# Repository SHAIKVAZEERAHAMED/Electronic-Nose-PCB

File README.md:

# Electronic Nose System

A compact 14-channel MEMS-based Electronic Nose (E-Nose) platform designed for multi-gas sensing applications. The system integrates analog signal acquisition, dual-microcontroller processing, heater control, and battery-powered operation on a custom-designed PCB developed using KiCad.

---

## Overview

The Electronic Nose System is a modular hardware platform designed to interface with fourteen MEMS gas sensors for detecting a wide range of volatile organic compounds (VOCs) and hazardous gases. The design combines dedicated analog front-end circuits, a dual-microcontroller architecture, and an efficient power management subsystem into a compact printed circuit board.

The project focuses on hardware architecture, PCB implementation, and modular subsystem design to support future gas classification and pattern recognition algorithms.

---

## Key Features

- 14-channel MEMS gas sensor array
- ESP32-S3 WROOM 1 N16 main controller
- RP2040 dedicated PWM co-processor
- Configurable analog front-end
- Battery-powered operation
- Dual heater voltage rails (1.8 V and 2.5 V)
- BME680 environmental sensing
- KiCad 9.0.7 PCB design
- Modular hardware architecture

---

## System Architecture

```text
                    +----------------------+
                    |   MEMS Gas Sensors   |
                    +----------+-----------+
                               |
                               v
                    +----------------------+
                    |  Analog Front End    |
                    +----------+-----------+
                               ^
                               |
                              SPI
                               |
                               v
                    +----------------------+
                    |   ESP32-S3 (Master)  |
                    +----+--+---------+----+
                         |  ^         |
                         |  |         |
                      UART SPI       I²C/ADC
                         |  |         |
                         v  v         v
                  +--------------+  BME680
                  |    RP2040    |
                  +------+-------+
                         |
                         v
                +------------------+
                |  Heater Driver   |
                +--------+---------+
                         |
                         v
                +------------------+
                |  MEMS Heaters    |
                +------------------+

          Power Management supplies all modules
```

---
---

## PCB Layout

### Top View

### 3D View

---

## Hardware Specifications

| Component | Description |
|-----------|-------------|
| Gas Sensors | 14 MEMS Gas Sensors |
| Main Controller | ESP32-S3 WROOM 1 N16 |
| PWM Controller | RP2040 |
| Heater Driver | TBD62083AFNG |
| Environmental Sensor | BME680 |
| Analog Front End | TLV9152 |
| PCB Software | KiCad 9.0.7 |
| Power Source | Rechargeable Li-ion Battery |

---

## Repository Structure

```text
Electronic-Nose-PCB
│
├── Hardware
│   ├── Sensors
│   ├── Analog_Front_End
│   ├── ESP32-S3
│   ├── RP2040
│   ├── Power_Management
│   ├── PCB
│   └── KiCad_Project
│
├── Documentation
├── Datasheets
└── README.md
```
---

## Hardware

The hardware design is divided into modular subsystems:

- MEMS Gas Sensor Array
- Analog Front-End
- ESP32-S3 Processing Unit
- RP2040 PWM Controller
- Heater Driver
- Battery Management
- PCB Layout

---

## Software

| Tool | Purpose |
|------|---------|
| KiCad 9.0.7 | PCB Design |
| GitHub | Version Control |

---

## Project Status

🚧 Under Development

Current progress:

- ✅ System Architecture
- ✅ Schematic Design
- ⏳ PCB Layout
- ⏳ PCB Fabrication
- ⏳ Hardware Testing
- ⏳ Firmware Development

---

## License

This project is intended for academic and research purposes.

---

## Acknowledgment

This work was carried out at the International Institute of Information Technology Bangalore (IIIT Bangalore) under the guidance of Prof. Kurian Polachan. Technical guidance and discussions from Prof. David Aleklett Kadish and David Cuartielles (Malmö University and Arduino Co-founder) are gratefully acknowledged.

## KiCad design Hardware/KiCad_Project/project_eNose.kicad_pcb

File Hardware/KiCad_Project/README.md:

# KiCad Project

This directory contains the complete KiCad project files for the Electronic Nose hardware.

## Overview

The Electronic Nose PCB was designed using **KiCad 9.0.7**. This folder includes all project files required to open, edit, verify, and manufacture the PCB.

## Software Version

- KiCad 9.0.7

## Project Files

| File | Description |
|------|-------------|
| *.kicad_pro | KiCad project file |
| *.kicad_sch | Complete schematic |
| *.kicad_pcb | PCB layout |

## Design Features

- Multi-sheet schematic
- Fourteen-channel MEMS gas sensor array
- Dual microcontroller architecture
- Analog front-end circuitry
- Power management subsystem
- Single-layer PCB layout
- Design Rule Check (DRC) in progress
- Electrical Rule Check (ERC) verified

## How to Open

1. Install **KiCad 9.0.7** or later.
2. Open the `.kicad_pro` file.
3. Use the Schematic Editor to view the circuit design.
4. Use the PCB Editor to inspect or modify the layout.

## Folder Contents

This folder will contain:

- KiCad project
- Schematics
- PCB layout

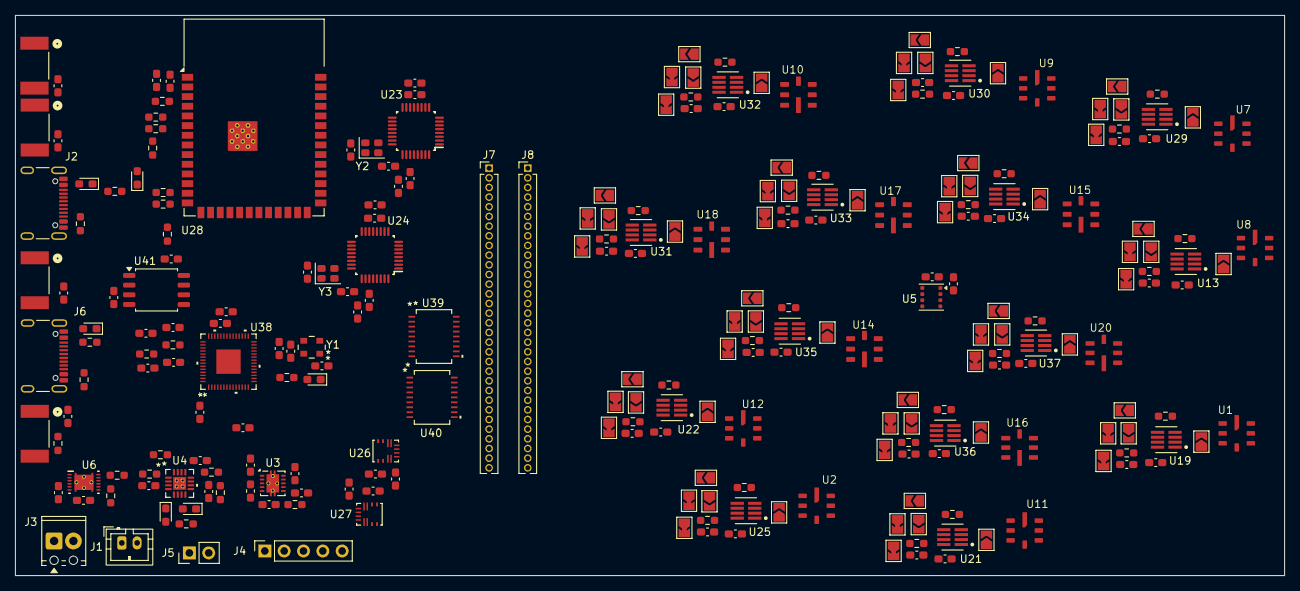
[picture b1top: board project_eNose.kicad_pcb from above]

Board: 2 copper layers, 166.7 x 73.6 mm, 262 parts (0 on the bottom side), 198 nets, no tracks yet.

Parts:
C1, C2, C4, C5, C9, C32, C41, C50: 0.1uF; C_0603_1608Metric_Pad1.08x0.95mm_HandSolder
C3, C60, C61, C62, C63, C64, C65, C66, C67, C68, C69, C70, C71, C72: 2.2nF; C_0603_1608Metric_Pad1.08x0.95mm_HandSolder
C6, C8, C10, C11, C12, C16, C17, C18, C19, C25, C26, C27, C31, C59: 10nF; C_0603_1608Metric_Pad1.08x0.95mm_HandSolder
C7, C13, C14, C20, C21, C22, C24: 10uF; C_0603_1608Metric_Pad1.08x0.95mm_HandSolder
C15, C23: 4.7uF; C_0603_1608Metric_Pad1.08x0.95mm_HandSolder
C28, C30, C38, C51, C52, C53, C54, C55, C56, C57, C58: 1uF; C_0603_1608Metric_Pad1.08x0.95mm_HandSolder
C29: 0.47uF; C_0603_1608Metric_Pad1.08x0.95mm_HandSolder
C33, C34, C35, C36, C37, C39, C40, C43, C44, C47, C73, C74: 100nF; C_0603_1608Metric_Pad1.08x0.95mm_HandSolder
C42: 22uF; C_0603_1608Metric_Pad1.08x0.95mm_HandSolder
C45, C46: 18pF; C_0603_1608Metric_Pad1.08x0.95mm_HandSolder
C48, C49: 220nF; C_0603_1608Metric_Pad1.08x0.95mm_HandSolder
D1, D2, D3, D4: LED; LED_0603_1608Metric_Pad1.05x0.95mm_HandSolder
D5, D6: D_Schottky; D_0603_1608Metric_Pad1.05x0.95mm_HandSolder
H1, H2, H3, H4: MountingHole; MountingHole_2mm
J1: Conn_01x02; JST_PH_B2B-PH-K_1x02_P2.00mm_Vertical
J2, J6: USB_C_Receptacle_USB2.0_16P; USB_C_Receptacle_GCT_USB4105-xx-A_16P_TopMnt_Horizontal
J3: Screw_Terminal_01x02; TerminalBlock_Phoenix_MPT-0,5-2-2.54_1x02_P2.54mm_Horizontal
J4: Conn_01x05; PinSocket_1x05_P2.54mm_Vertical
J5: Conn_01x02; PinHeader_1x02_P2.54mm_Vertical
J7, J8: Conn_01x32; PinHeader_1x32_P1.27mm_Vertical
JP1, JP2, JP45, JP46, JP47, JP48, JP49, JP50, JP51, JP52, JP53, JP54, JP55, JP56, JP57, JP58, JP59, JP60, JP61, JP62, JP63, JP64, JP65, JP66, JP67, JP68, JP69, JP70: SolderJumper_2_Bridged; SolderJumper-2_P1.3mm_Bridged_TrianglePad1.0x1.5mm_FIXED
JP3, JP4, JP5, JP6, JP7, JP8, JP9, JP10, JP11, JP12, JP13, JP14, JP15, JP16, JP17, JP18, JP19, JP20, JP21, JP22, JP23, JP24, JP25, JP26, JP27, JP28, JP29, JP30, JP31, JP32, JP33, JP34, JP35, JP36, JP37, JP38, JP39, JP40, JP41, JP42, JP43, JP44: SolderJumper_2_Open; SolderJumper-2_P1.3mm_Open_TrianglePad1.0x1.5mm
L1: 2.2uH; L_0603_1608Metric_Pad1.05x0.95mm_HandSolder
R1, R2, R4, R11, R15, R18, R19, R22, R23, R24, R25, R26, R27, R28, R29, R30, R31, R32, R33, R34, R35, R36, R37, R38, R39, R40, R41, R42, R43, R44, R45, R82: 10K; R_0603_1608Metric_Pad0.98x0.95mm_HandSolder
R3: 100E; R_0603_1608Metric_Pad0.98x0.95mm_HandSolder
R5, R6, R81: 1K; R_0603_1608Metric_Pad0.98x0.95mm_HandSolder
R7: 1.13K; R_0603_1608Metric_Pad0.98x0.95mm_HandSolder
R8: 1.18K; R_0603_1608Metric_Pad0.98x0.95mm_HandSolder
R9: 0.01; R_0603_1608Metric_Pad0.98x0.95mm_HandSolder
R10, R12, R13: 4.7K; R_0603_1608Metric_Pad0.98x0.95mm_HandSolder
R14: 820E; R_0603_1608Metric_Pad0.98x0.95mm_HandSolder
R16, R17: 22E; R_0603_1608Metric_Pad0.98x0.95mm_HandSolder
R20, R21, R52, R53: 5.1K; R_0603_1608Metric_Pad0.98x0.95mm_HandSolder
R79, R80: 27E; R_0603_1608Metric_Pad0.98x0.95mm_HandSolder
SW1, SW2, SW3, SW4: KSS221GLFS; SW_KSS221GLFS_CNK
U1, U2, U7, U8, U9, U11, U12: SMD_Series
U3: TPS63001; Texas_DRC0010J_ThermalVias
U4: BQ24075RGTR; RGT16_1P7X1P7
U5: BME680; Bosch_LGA-8_3x3mm_P0.8mm_ClockwisePinNumbering
U6: BQ27441DRZR-G1A; DRZ0012A
U10, U14, U15, U17, U18: GM_Series; GM102B
U13, U19, U21, U22, U25, U29, U30, U31, U32, U33, U34, U35, U36, U37: TLV9152; DDF0008A-IPC_A
U16, U20: GM_Series; GM202_502B
U23, U24: ADS131M08IPBSR; PBS0032A_L
U26: MPM3805GQB-25-Z; QFN2p5x3p0x0p9_MNP
U27: MPM3805GQB-18-P; QFN2p5x3p0x0p9_MNP
U28: ESP32-S3-WROOM-1-N16; ESP32-S3-WROOM-1
U38: SC091413; QFN56_7X7_RPI-L
U39, U40: TBD62083AFNG_EL; SSOP18-P-225-0p65_TOS-L
U41: W25Q32JVSS; SOIC-8_5.3x5.3mm_P1.27mm
Y1: ABM8G-12.000MHZ-18-D2Y-T; CRYSTAL_ABM8G_ABR-L
Y2, Y3: SG-210STF; Oscillator_SMD_SeikoEpson_SG210-4Pin_2.5x2.0mm

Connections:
1p8V: C22.1, C34.2, J7.31, J8.31, U1.1 (VH+), U2.1 (VH+), U7.1 (VH+), U8.1 (VH+), U9.1 (VH+), U10.1 (VH+), U11.1 (VH+), U12.1 (VH+), U18.1 (VH+), U27.5 (OUT), U27.6 (OUT), U27.12 (OUT_S), U41.8 (VCC)
2p5V: C20.1, J7.30, J8.30, U14.1 (VH+), U15.1 (VH+), U16.1 (VH+), U17.1 (VH+), U20.1 (VH+), U26.5 (OUT), U26.6 (OUT), U26.12 (OUT_S)
3p3V: C4.1, C5.1, C6.2, C8.2, C10.2, C11.2, C12.2, C13.1, C14.1, C16.2, C17.2, C18.2, C19.2, C25.2, C26.2, C27.2, C31.2, C33.2, C35.2, C36.2, C37.2, C38.2, C39.2, C40.2, C41.2, C42.2, C43.2, C44.2, C47.2, C51.2, C52.2, C53.2, C54.2, C55.2, C56.2, C57.2, C58.2, C59.2, C73.2, C74.1, J4.1, J7.29, J8.29, R10.1, R12.1, R13.1, R15.1, R82.2, U1.2 (VCC), U2.2 (VCC), U3.1 (VOUT), U3.10 (FB), U5.2 (CSB), U5.6 (VDDIO), U5.8 (VDD), U7.2 (VCC), U8.2 (VCC), U9.2 (VCC), U10.7 (VCC), U11.2 (VCC), U12.2 (VCC), U13.8 (V+), U14.7 (VCC), U15.7 (VCC), U16.7 (VCC), U17.7 (VCC), U18.7 (VCC), U19.8 (V+), U20.7 (VCC), U21.8 (V+), U22.8 (V+), U23.14 (REFIN), U23.15 (AVDD), U23.26 (IOVDD), U23.27 (AVDD), U24.14 (REFIN), U24.15 (AVDD), U24.26 (IOVDD), U24.27 (AVDD), U25.8 (V+), U28.2 (3V3), U29.8 (V+), U30.8 (V+), U31.8 (V+), U32.8 (V+), U33.8 (V+), U34.8 (V+), U35.8 (V+), U36.8 (V+), U37.8 (V+), U38.1 (IOVDD), U38.10 (IOVDD), U38.22 (IOVDD), U38.33 (IOVDD), U38.42 (IOVDD), U38.43 (ADC_AVDD), U38.44 (VREG_VIN), U38.48 (USB_VDD), U38.49 (IOVDD), Y2.4 (Vcc), Y3.4 (Vcc)
/Acetone/OUT1: JP16.1 (A), JP17.1 (A), U29.1 (1OUT), U29.2 (1IN-), U29.5 (2IN+)
/Alcohol/OUT1: JP34.1 (A), JP35.1 (A), U35.1 (1OUT), U35.2 (1IN-), U35.5 (2IN+)
/BME680 (Temp., Air, Humidity)/I2C.SCL: R13.2, U5.4 (SCK), U6.2 (SCL), U28.6 (IO6)
/BME680 (Temp., Air, Humidity)/I2C.SDA: R12.2, U5.3 (SDI), U6.1 (SDA), U28.5 (IO5)
/Breath Smell/OUT1: JP31.1 (A), JP32.1 (A), U34.1 (1OUT), U34.2 (1IN-), U34.5 (2IN+)
/CH4/OUT1: JP10.1 (A), JP11.1 (A), U22.1 (1OUT), U22.2 (1IN-), U22.5 (2IN+)
/Charger-Regulator/BatP: C15.1, C29.2, C30.1, J1.1, J3.1, J5.1, R9.1, U4.2 (BAT), U4.3 (BAT), U6.5 (VDD), U6.6 (BAT), U6.8 (SRP)
/Charger-Regulator/VIN: C28.1, D5.1 (K), D6.1 (K), U4.13 (IN)
/Charger-Regulator/VSYS: C7.1, C21.1, C23.1, C24.1, R3.1, R6.2, R9.2, U3.5 (VIN), U4.5 (EN2), U4.10 (OUT), U4.11 (OUT), U6.7 (SRN), U26.7 (VIN), U26.9 (EN), U27.7 (VIN), U27.9 (EN)
/H2/OUT1: JP28.1 (A), JP29.1 (A), U33.1 (1OUT), U33.2 (1IN-), U33.5 (2IN+)
/H2S & Benzene/OUT1: JP25.1 (A), JP26.1 (A), U32.1 (1OUT), U32.2 (1IN-), U32.5 (2IN+)
/H2S/OUT1: JP7.1 (A), JP8.1 (A), U25.1 (1OUT), U25.2 (1IN-), U25.5 (2IN+)
/HCHO/OUT1: JP3.1 (A), JP43.1 (A), U13.1 (1OUT), U13.2 (1IN-), U13.5 (2IN+)
/NH3/OUT1: JP4.1 (A), JP5.1 (A), U19.1 (1OUT), U19.2 (1IN-), U19.5 (2IN+)
/NO2/OUT1: JP22.1 (A), JP23.1 (A), U31.1 (1OUT), U31.2 (1IN-), U31.5 (2IN+)
/Perforated-Connectors/A0: C3.2, J7.1, J8.1, R23.2, U13.7 (2OUT), U23.29 (AIN0P)
/Perforated-Connectors/A1: C60.2, J7.2, J8.2, R11.2, U19.7 (2OUT), U23.32 (AIN1P)
/Perforated-Connectors/A2: C61.2, J7.3, J8.3, R19.2, U23.1 (AIN2P), U25.7 (2OUT)
/Perforated-Connectors/A3: C62.2, J7.4, J8.4, R25.2, U22.7 (2OUT), U23.4 (AIN3P)
/Perforated-Connectors/A4: C63.2, J7.5, J8.5, R27.2, U21.7 (2OUT), U23.5 (AIN4P)
/Perforated-Connectors/A5: C64.2, J7.6, J8.6, R29.2, U23.8 (AIN5P), U29.7 (2OUT)
/Perforated-Connectors/A6: C65.2, J7.7, J8.7, R31.2, U23.9 (AIN6P), U30.7 (2OUT)
/Perforated-Connectors/A7: C66.2, J7.8, J8.8, R33.2, U24.29 (AIN0P), U31.7 (2OUT)
/Perforated-Connectors/A8: C67.2, J7.9, J8.9, R35.2, U24.32 (AIN1P), U32.7 (2OUT)
/Perforated-Connectors/A9: C68.2, J7.10, J8.10, R37.2, U24.1 (AIN2P), U33.7 (2OUT)
/Perforated-Connectors/A10: C69.2, J7.11, J8.11, R39.2, U24.4 (AIN3P), U34.7 (2OUT)
/Perforated-Connectors/A11: C70.2, J7.12, J8.12, R41.2, U24.5 (AIN4P), U35.7 (2OUT)
/Perforated-Connectors/A12: C71.2, J7.13, J8.13, R43.2, U24.8 (AIN5P), U36.7 (2OUT)
/Perforated-Connectors/A13: C72.2, J7.14, J8.14, R45.2, U24.9 (AIN6P), U37.7 (2OUT)
/Perforated-Connectors/HOT0: J7.15, J8.15, U8.7 (HOT), U39.18 (O1)
/Perforated-Connectors/HOT1: J7.16, J8.16, U1.7 (HOT), U39.17 (O2)
/Perforated-Connectors/HOT2: J7.17, J8.17, U2.7 (HOT), U39.16 (O3)
/Perforated-Connectors/HOT3: J7.18, J8.18, U12.7 (HOT), U39.15 (O4)
/Perforated-Connectors/HOT4: J7.19, J8.19, U11.7 (HOT), U39.14 (O5)
/Perforated-Connectors/HOT5: J7.20, J8.20, U7.7 (HOT), U39.13 (O6)
/Perforated-Connectors/HOT6: J7.21, J8.21, U9.7 (HOT), U39.12 (O7)
/Perforated-Connectors/HOT7: J7.22, J8.22, U18.3 (HOT), U40.18 (O1)
/Perforated-Connectors/HOT8: J7.23, J8.23, U10.3 (HOT), U40.17 (O2)
/Perforated-Connectors/HOT9: J7.24, J8.24, U17.3 (HOT), U40.16 (O3)
/Perforated-Connectors/HOT10: J7.25, J8.25, U15.3 (HOT), U40.15 (O4)
/Perforated-Connectors/HOT11: J7.26, J8.26, U14.3 (HOT), U40.14 (O5)
/Perforated-Connectors/HOT12: J7.27, J8.27, U16.3 (HOT), U40.13 (O6)
/Perforated-Connectors/HOT13: J7.28, J8.28, U20.3 (HOT), U40.12 (O7)
/Propane/OUT1: JP13.1 (A), JP14.1 (A), U21.1 (1OUT), U21.2 (1IN-), U21.5 (2IN+)
/RP2040/CLK: U38.52 (SQPI_SCLK), U41.6 (CLK)
/RP2040/CS: U38.56 (SQPI_SS_N), U41.1 (~CS)
/RP2040/DVDD: U38.23 (DVDD), U38.45 (VREG_VOUT), U38.50 (DVDD)
/RP2040/IO0: U38.53 (SQPI_SD0), U41.5 (DI/IO_{0})
/RP2040/IO1: U38.55 (SQPI_SD1), U41.2 (DO/IO_{1})
/RP2040/IO2: U38.54 (SQPI_SD2), U41.3 (~WP/IO_{2})
/RP2040/IO3: U38.51 (SQPI_SD3), U41.7 (~HOLD/~RESET/IO_{3})
/RP2040/PWM0: U38.2 (GPIO0), U39.1 (I1)
/RP2040/PWM1: U38.3 (GPIO1), U39.2 (I2)
/RP2040/PWM2: U38.4 (GPIO2), U39.3 (I3)
/RP2040/PWM3: U38.5 (GPIO3), U39.4 (I4)
/RP2040/PWM4: U38.6 (GPIO4), U39.5 (I5)
/RP2040/PWM5: U38.7 (GPIO5), U39.6 (I6)
/RP2040/PWM6: U38.8 (GPIO6), U39.7 (I7)
/RP2040/PWM7: U38.9 (GPIO7), U40.1 (I1)
/RP2040/PWM8: U38.11 (GPIO8), U40.2 (I2)
/RP2040/PWM9: U38.12 (GPIO9), U40.3 (I3)
/RP2040/PWM10: U38.13 (GPIO10), U40.4 (I4)
/RP2040/PWM11: U38.14 (GPIO11), U40.5 (I5)
/RP2040/PWM12: U38.15 (GPIO12), U40.6 (I6)
/RP2040/PWM13: U38.16 (GPIO13), U40.7 (I7)
/RP2040/RUN_RESET: C32.2, J4.5, R82.1, SW3.2, U38.26 (RUN)
/RP2040/SPI0: U28.39 (IO1), U38.32 (GPIO21)
/RP2040/SPI1: U28.38 (IO2), U38.31 (GPIO20)
/RP2040/SPI2: U28.10 (IO17), U38.30 (GPIO19)
/RP2040/SPI3: U28.11 (IO18), U38.29 (GPIO18)
/RP2040/SWD_IO: J4.3, U38.25 (SWDIO)
/RP2040/SW_CLK: J4.4, U38.24 (SWCLK)
/RP2040/UART.Rx: U28.37 (TXD0), U38.28 (GPIO17)
/RP2040/UART.Tx: U28.36 (RXD0), U38.27 (GPIO16)
/RP2040/USB1.Dm: J6.A7 (D-), J6.B7 (D-), R80.1
/RP2040/USB1.Dp: J6.A6 (D+), J6.B6 (D+), R79.2
/RP2040/XIN: C45.2, U38.20 (XIN), Y1.1
/RP2040/XOUT: C46.2, U38.21 (XOUT), Y1.3
/Smoke/OUT1: JP37.1 (A), JP38.1 (A), U36.1 (1OUT), U36.2 (1IN-), U36.5 (2IN+)
/TVOC/OUT1: JP19.1 (A), JP20.1 (A), U30.1 (1OUT), U30.2 (1IN-), U30.5 (2IN+)
/VOC/OUT1: JP40.1 (A), JP41.1 (A), U37.1 (1OUT), U37.2 (1IN-), U37.5 (2IN+)
/bat-conn-Monitor/GPOUT: R10.2, U6.12 (GPOUT), U28.15 (IO3)
/esp/Analog -> SPI/A_SPI0: U23.21 (DIN), U24.21 (DIN), U28.19 (IO11)
/esp/Analog -> SPI/A_SPI1: U23.20 (DOUT), U24.20 (DOUT), U28.21 (IO13)
/esp/Analog -> SPI/A_SPI2: U23.19 (SCLK), U24.19 (SCLK), U28.20 (IO12)
/esp/Analog -> SPI/A_SPI3: U23.18 (DRDY_N), U28.17 (IO9)
/esp/Analog -> SPI/A_SPI4: U23.17 (CS_N), U28.18 (IO10)
/esp/Analog -> SPI/A_SPI5: U23.16 (SYNC_RESET_N), U28.12 (IO8)
/esp/Analog -> SPI/A_SPI6: U24.18 (DRDY_N), U28.22 (IO14)
/esp/Analog -> SPI/A_SPI7: U24.17 (CS_N), U28.8 (IO15)
/esp/Analog -> SPI/A_SPI8: U24.16 (SYNC_RESET_N), U28.9 (IO16)
/esp/Analog -> SPI/CLKIN1: U23.23 (XTAL1_CLKIN), Y2.3 (OUT)
/esp/Analog -> SPI/CLKIN2: U24.23 (XTAL1_CLKIN), Y3.3 (OUT)
/esp/EN: C1.2, C2.2, R15.2, SW1.2, SW2.2, U28.3 (EN), U28.27 (IO0)
/esp/USB0.Dm: J2.A7 (D-), J2.B7 (D-), R17.1
/esp/USB0.Dp: J2.A6 (D+), J2.B6 (D+), R16.2
/esp/user_sw: C50.2, SW4.2, U28.4 (IO4)
GND: C1.1, C2.1, C4.2, C5.2, C6.1, C7.2, C8.1, C9.2, C10.1, C11.1, C12.1, C13.2, C14.2, C15.2, C16.1, C17.1, C18.1, C19.1, C20.2, C21.2, C22.2, C23.2, C24.2, C25.1, C26.1, C27.1, C28.2, C29.1, C30.2, C31.1, C32.1, C33.1, C34.1, C35.1, C36.1, C37.1, C38.1, C39.1, C40.1, C41.1, C42.1, C43.1, C44.1, C45.1, C46.1, C47.1, C48.1, C49.1, C50.1, C51.1, C52.1, C53.1, C54.1, C55.1, C56.1, C57.1, C58.1, C59.1, C73.1, C74.2, D1.1 (K), D4.1 (K), J1.2, J2.A1 (GND), J2.A12 (GND), J2.B1 (GND), J2.B12 (GND), J2.S1 (SHIELD), J3.2, J4.2, J5.2, J6.A1 (GND), J6.A12 (GND), J6.B1 (GND), J6.B12 (GND), J6.S1 (SHIELD), J7.32, J8.32, R1.1, R2.1, R4.1, R7.1, R8.1, R18.1, R20.2, R21.1, R22.1, R24.1, R26.1, R28.1, R30.1, R32.1, R34.1, R36.1, R38.1, R40.1, R42.1, R44.1, R52.2, R53.1, SW1.1, SW2.1, SW3.1, SW4.1, U3.3 (PGND), U3.9 (GND), U3.11 (PGND), U4.4 (*CE), U4.6 (EN1), U4.8 (VSS), U4.14 (TMR), U4.15 (SYSOFF), U4.17 (EPAD), U5.1 (GND), U5.5 (SDO), U5.7 (GND), U6.3 (VSS), U6.13 (PAD), U13.4 (V-), U19.4 (V-), U21.4 (V-), U22.4 (V-), U23.2 (AIN2N), U23.3 (AIN3N), U23.6 (AIN4N), U23.7 (AIN5N), U23.10 (AIN6N), U23.11 (AIN7N), U23.12 (AIN7P), U23.13 (AGND_REFGND), U23.25 (DGND), U23.28 (AGND), U23.30 (AIN0N), U23.31 (AIN1N), U24.2 (AIN2N), U24.3 (AIN3N), U24.6 (AIN4N), U24.7 (AIN5N), U24.10 (AIN6N), U24.11 (AIN7N), U24.12 (AIN7P), U24.13 (AGND_REFGND), U24.25 (DGND), U24.28 (AGND), U24.30 (AIN0N), U24.31 (AIN1N), U25.4 (V-), U26.1 (PGND), U26.2 (PGND), U26.11 (AGND), U27.1 (PGND), U27.2 (PGND), U27.11 (AGND), U28.1 (GND), U28.40 (GND), U28.41 (GND), U29.4 (V-), U30.4 (V-), U31.4 (V-), U32.4 (V-), U33.4 (V-), U34.4 (V-), U35.4 (V-), U36.4 (V-), U37.4 (V-), U38.19 (TESTEN), U38.35 (GPIO23), U38.57 (GND), U39.9 (GND), U40.9 (GND), U41.4 (GND), Y1.2, Y1.4, Y2.1 (~ST), Y2.2 (GND), Y3.1 (~ST), Y3.2 (GND)
unnamed: D1.2 (A), R14.2
unnamed: D2.2 (A), R5.2
unnamed: D2.1 (K), U4.7 (*PGOOD)
unnamed: D3.2 (A), R5.1, R6.1
unnamed: D3.1 (K), U4.9 (*CHG)
unnamed: D4.2 (A), R81.2
unnamed: D5.2 (A), J6.A4 (VBUS), J6.A9 (VBUS), J6.B4 (VBUS), J6.B9 (VBUS)
unnamed: D6.2 (A), J2.A4 (VBUS), J2.A9 (VBUS), J2.B4 (VBUS), J2.B9 (VBUS)
unnamed: J2.A5 (CC1), R20.1
unnamed: J2.B5 (CC2), R21.2
unnamed: J6.A5 (CC1), R52.1
unnamed: J6.B5 (CC2), R53.2
unnamed: JP1.1 (A), JP2.1 (A), JP43.2 (B), JP44.2 (B), U13.6 (2IN-)
unnamed: JP1.2 (B), R23.1
unnamed: C3.1, JP2.2 (B)
unnamed: JP3.2 (B), U8.8 (VOUT), U13.3 (1IN+)
unnamed: JP4.2 (B), U1.8 (VOUT), U19.3 (1IN+)
unnamed: JP6.1 (A), R2.2
unnamed: JP7.2 (B), U2.8 (VOUT), U25.3 (1IN+)
unnamed: JP9.1 (A), R18.2
unnamed: JP10.2 (B), U12.8 (VOUT), U22.3 (1IN+)
unnamed: JP11.2 (B), JP12.2 (B), JP49.1 (A), JP50.1 (A), U22.6 (2IN-)
unnamed: JP12.1 (A), R24.2
unnamed: JP13.2 (B), U11.8 (VOUT), U21.3 (1IN+)
unnamed: JP14.2 (B), JP15.2 (B), JP51.1 (A), JP52.1 (A), U21.6 (2IN-)
unnamed: JP15.1 (A), R26.2
unnamed: JP16.2 (B), U7.8 (VOUT), U29.3 (1IN+)
unnamed: JP17.2 (B), JP18.2 (B), JP53.1 (A), JP54.1 (A), U29.6 (2IN-)
unnamed: JP18.1 (A), R28.2
unnamed: JP19.2 (B), U9.8 (VOUT), U30.3 (1IN+)
unnamed: JP20.2 (B), JP21.2 (B), JP55.1 (A), JP56.1 (A), U30.6 (2IN-)
unnamed: JP21.1 (A), R30.2
unnamed: JP22.2 (B), U18.5 (VOUT), U31.3 (1IN+)
unnamed: JP23.2 (B), JP24.2 (B), JP57.1 (A), JP58.1 (A), U31.6 (2IN-)
unnamed: JP24.1 (A), R32.2
unnamed: JP25.2 (B), U10.5 (VOUT), U32.3 (1IN+)
unnamed: JP26.2 (B), JP27.2 (B), JP59.1 (A), JP60.1 (A), U32.6 (2IN-)
unnamed: JP27.1 (A), R34.2
unnamed: JP28.2 (B), U17.5 (VOUT), U33.3 (1IN+)
unnamed: JP29.2 (B), JP30.2 (B), JP61.1 (A), JP62.1 (A), U33.6 (2IN-)
unnamed: JP30.1 (A), R36.2
unnamed: JP31.2 (B), U15.5 (VOUT), U34.3 (1IN+)
unnamed: JP32.2 (B), JP33.2 (B), JP63.1 (A), JP64.1 (A), U34.6 (2IN-)
unnamed: JP33.1 (A), R38.2
unnamed: JP34.2 (B), U14.5 (VOUT), U35.3 (1IN+)
unnamed: JP35.2 (B), JP36.2 (B), JP65.1 (A), JP66.1 (A), U35.6 (2IN-)
unnamed: JP36.1 (A), R40.2
unnamed: JP37.2 (B), U16.5 (VOUT), U36.3 (1IN+)
unnamed: JP38.2 (B), JP39.2 (B), JP67.1 (A), JP68.1 (A), U36.6 (2IN-)
unnamed: JP39.1 (A), R42.2
unnamed: JP40.2 (B), U20.5 (VOUT), U37.3 (1IN+)
unnamed: JP41.2 (B), JP42.2 (B), JP69.1 (A), JP70.1 (A), U37.6 (2IN-)
unnamed: JP42.1 (A), R44.2
unnamed: JP44.1 (A), R22.2
unnamed: JP5.2 (B), JP6.2 (B), JP45.1 (A), JP46.1 (A), U19.6 (2IN-)
unnamed: JP45.2 (B), R11.1
unnamed: C60.1, JP46.2 (B)
unnamed: JP8.2 (B), JP9.2 (B), JP47.1 (A), JP48.1 (A), U25.6 (2IN-)
unnamed: JP47.2 (B), R19.1
unnamed: C61.1, JP48.2 (B)
unnamed: JP49.2 (B), R25.1
unnamed: C62.1, JP50.2 (B)
unnamed: JP51.2 (B), R27.1
unnamed: C63.1, JP52.2 (B)
unnamed: JP53.2 (B), R29.1
unnamed: C64.1, JP54.2 (B)
unnamed: JP55.2 (B), R31.1
unnamed: C65.1, JP56.2 (B)
unnamed: JP57.2 (B), R33.1
unnamed: C66.1, JP58.2 (B)
unnamed: JP59.2 (B), R35.1
unnamed: C67.1, JP60.2 (B)
unnamed: JP61.2 (B), R37.1
unnamed: C68.1, JP62.2 (B)
unnamed: JP63.2 (B), R39.1
unnamed: C69.1, JP64.2 (B)
unnamed: JP65.2 (B), R41.1
unnamed: C70.1, JP66.2 (B)
unnamed: JP67.2 (B), R43.1
unnamed: C71.1, JP68.2 (B)
unnamed: JP69.2 (B), R45.1
unnamed: C72.1, JP70.2 (B)
unnamed: C9.1, R3.2, U3.6 (EN), U3.7 (PS/SYNC), U3.8 (VINA)
unnamed: L1.2, U3.4 (L1)
unnamed: L1.1, U3.2 (L2)
unnamed: R8.2, U4.12 (ILIM)
unnamed: R7.2, U4.16 (ISET)
unnamed: R4.2, U4.1 (TS)
unnamed: R1.2, U6.10 (BIN)
unnamed: C48.2, U23.24 (LDOCAP)
unnamed: C49.2, U24.24 (LDOCAP)
unnamed: R14.1, U28.7 (IO7)
unnamed: R17.2, U28.14 (USB_D+)
unnamed: R16.1, U28.13 (USB_D-)
unnamed: R81.1, U38.17 (GPIO14)
unnamed: R80.2, U38.46 (USB_DM)
unnamed: R79.1, U38.47 (USB_DP)

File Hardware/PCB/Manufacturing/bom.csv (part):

"Reference","Value","Footprint","myMANUFACTURER","myMPN"
"C1","0.1uF","Capacitor_SMD:C_0603_1608Metric_Pad1.08x0.95mm_HandSolder","YAGEO","CC0603MRY5V9BB104"
"C2","0.1uF","Capacitor_SMD:C_0603_1608Metric_Pad1.08x0.95mm_HandSolder","YAGEO","CC0603MRY5V9BB104"
"C3","2.2nF","Capacitor_SMD:C_0603_1608Metric_Pad1.08x0.95mm_HandSolder","KEMET","C0603X222F4HACTU"
"C4","0.1uF","Capacitor_SMD:C_0603_1608Metric_Pad1.08x0.95mm_HandSolder","YAGEO","CC0603MRY5V9BB104"
"C5","0.1uF","Capacitor_SMD:C_0603_1608Metric_Pad1.08x0.95mm_HandSolder","YAGEO","CC0603MRY5V9BB104"
"C6","10nF","Capacitor_SMD:C_0603_1608Metric_Pad1.08x0.95mm_HandSolder","Murata Electronics","GCM188R71H103KA37J"
"C7","10uF","Capacitor_SMD:C_0603_1608Metric_Pad1.08x0.95mm_HandSolder","Walsin Technology Corporation","0603X106M100CT"
"C8","10nF","Capacitor_SMD:C_0603_1608Metric_Pad1.08x0.95mm_HandSolder","Murata Electronics","GCM188R71H103KA37J"
"C9","0.1uF","Capacitor_SMD:C_0603_1608Metric_Pad1.08x0.95mm_HandSolder","YAGEO","CC0603MRY5V9BB104"
"C10","10nF","Capacitor_SMD:C_0603_1608Metric_Pad1.08x0.95mm_HandSolder","Murata Electronics","GCM188R71H103KA37J"
"C11","10nF","Capacitor_SMD:C_0603_1608Metric_Pad1.08x0.95mm_HandSolder","Murata Electronics","GCM188R71H103KA37J"
"C12","10nF","Capacitor_SMD:C_0603_1608Metric_Pad1.08x0.95mm_HandSolder","Murata Electronics","GCM188R71H103KA37J"
"C13","10uF","Capacitor_SMD:C_0603_1608Metric_Pad1.08x0.95mm_HandSolder","Walsin Technology Corporation","0603X106M100CT"
"C14","10uF","Capacitor_SMD:C_0603_1608Metric_Pad1.08x0.95mm_HandSolder","Walsin Technology Corporation","0603X106M100CT"
"C15","4.7uF","Capacitor_SMD:C_0603_1608Metric_Pad1.08x0.95mm_HandSolder","YAGEO","CC0603KRX5R6BB475"
"C16","10nF","Capacitor_SMD:C_0603_1608Metric_Pad1.08x0.95mm_HandSolder","Murata Electronics","GCM188R71H103KA37J"
"C17","10nF","Capacitor_SMD:C_0603_1608Metric_Pad1.08x0.95mm_HandSolder","Murata Electronics","GCM188R71H103KA37J"
"C18","10nF","Capacitor_SMD:C_0603_1608Metric_Pad1.08x0.95mm_HandSolder","Murata Electronics","GCM188R71H103KA37J"
"C19","10nF","Capacitor_SMD:C_0603_1608Metric_Pad1.08x0.95mm_HandSolder","Murata Electronics","GCM188R71H103KA37J"
"C20","10uF","Capacitor_SMD:C_0603_1608Metric_Pad1.08x0.95mm_HandSolder","Walsin Technology Corporation","0603X106M100CT"
"C21","10uF","Capacitor_SMD:C_0603_1608Metric_Pad1.08x0.95mm_HandSolder","Walsin Technology Corporation","0603X106M100CT"
"C22","10uF","Capacitor_SMD:C_0603_1608Metric_Pad1.08x0.95mm_HandSolder","Walsin Technology Corporation","0603X106M100CT"
"C23","4.7uF","Capacitor_SMD:C_0603_1608Metric_Pad1.08x0.95mm_HandSolder","YAGEO","CC0603KRX5R6BB475"
"C24","10uF","Capacitor_SMD:C_0603_1608Metric_Pad1.08x0.95mm_HandSolder","Walsin Technology Corporation","0603X106M100CT"
"C25","10nF","Capacitor_SMD:C_0603_1608Metric_Pad1.08x0.95mm_HandSolder","Murata Electronics","GCM188R71H103KA37J"
"C26","10nF","Capacitor_SMD:C_0603_1608Metric_Pad1.08x0.95mm_HandSolder","Murata Electronics","GCM188R71H103KA37J"
"C27","10nF","Capacitor_SMD:C_0603_1608Metric_Pad1.08x0.95mm_HandSolder","Murata Electronics","GCM188R71H103KA37J"
"C28","1uF","Capacitor_SMD:C_0603_1608Metric_Pad1.08x0.95mm_HandSolder","YAGEO","CC0603KRX7R7BB105"
"C29","0.47uF","Capacitor_SMD:C_0603_1608Metric_Pad1.08x0.95mm_HandSolder","YAGEO","CC0603KRX5R8BB474"
"C30","1uF","Capacitor_SMD:C_0603_1608Metric_Pad1.08x0.95mm_HandSolder","YAGEO","CC0603KRX7R7BB105"
"C31","10nF","Capacitor_SMD:C_0603_1608Metric_Pad1.08x0.95mm_HandSolder","Murata Electronics","GCM188R71H103KA37J"
"C32","0.1uF","Capacitor_SMD:C_0603_1608Metric_Pad1.08x0.95mm_HandSolder","YAGEO","CC0603MRY5V9BB104"
"C33","100nF","Capacitor_SMD:C_0603_1608Metric_Pad1.08x0.95mm_HandSolder","YAGEO","CC0603MRX7R9BB104"
"C34","100nF","Capacitor_SMD:C_0603_1608Metric_Pad1.08x0.95mm_HandSolder","YAGEO","CC0603MRX7R9BB104"
"C35","100nF","Capacitor_SMD:C_0603_1608Metric_Pad1.08x0.95mm_HandSolder","YAGEO","CC0603MRX7R9BB104"
"C36","100nF","Capacitor_SMD:C_0603_1608Metric_Pad1.08x0.95mm_HandSolder","YAGEO","CC0603MRX7R9BB104"
"C37","100nF","Capacitor_SMD:C_0603_1608Metric_Pad1.08x0.95mm_HandSolder","YAGEO","CC0603MRX7R9BB104"
"C38","1uF","Capacitor_SMD:C_0603_1608Metric_Pad1.08x0.95mm_HandSolder","YAGEO","CC0603KRX7R7BB105"
"C39","100nF","Capacitor_SMD:C_0603_1608Metric_Pad1.08x0.95mm_HandSolder","YAGEO","CC0603MRX7R9BB104"
"C40","100nF","Capacitor_SMD:C_0603_1608Metric_Pad1.08x0.95mm_HandSolder","YAGEO","CC0603MRX7R9BB104"
"C41","0.1uF","Capacitor_SMD:C_0603_1608Metric_Pad1.08x0.95mm_HandSolder","YAGEO","CC0603MRY5V9BB104"
"C42","22uF","Capacitor_SMD:C_0603_1608Metric_Pad1.08x0.95mm_HandSolder","YAGEO","CC0603MRX5R6BB226"
"C43","100nF","Capacitor_SMD:C_0603_1608Metric_Pad1.08x0.95mm_HandSolder","YAGEO","CC0603MRX7R9BB104"
"C44","100nF","Capacitor_SMD:C_0603_1608Metric_Pad1.08x0.95mm_HandSolder","YAGEO","CC0603MRX7R9BB104"
"C45","18pF","Capacitor_SMD:C_0603_1608Metric_Pad1.08x0.95mm_HandSolder","Murata Electronics","GRM1885C2A180JA01D"
"C46","18pF","Capacitor_SMD:C_0603_1608Metric_Pad1.08x0.95mm_HandSolder","Murata Electronics","GRM1885C2A180JA01D"
"C47","100nF","Capacitor_SMD:C_0603_1608Metric_Pad1.08x0.95mm_HandSolder","YAGEO","CC0603MRX7R9BB104"
"C48","220nF","Capacitor_SMD:C_0603_1608Metric_Pad1.08x0.95mm_HandSolder","KEMET","C0603C224K3RACTU"
"C49","220nF","Capacitor_SMD:C_0603_1608Metric_Pad1.08x0.95mm_HandSolder","KEMET","C0603C224K3RACTU"
"C50","0.1uF","Capacitor_SMD:C_0603_1608Metric_Pad1.08x0.95mm_HandSolder","YAGEO","CC0603MRY5V9BB104"
"C51","1uF","Capacitor_SMD:C_0603_1608Metric_Pad1.08x0.95mm_HandSolder","YAGEO","CC0603KRX7R7BB105"
"C52","1uF","Capacitor_SMD:C_0603_1608Metric_Pad1.08x0.95mm_HandSolder","YAGEO","CC0603KRX7R7BB105"
"C53","1uF","Capacitor_SMD:C_0603_1608Metric_Pad1.08x0.95mm_HandSolder","YAGEO","CC0603KRX7R7BB105"
"C54","1uF","Capacitor_SMD:C_0603_1608Metric_Pad1.08x0.95mm_HandSolder","YAGEO","CC0603KRX7R7BB105"
"C55","1uF","Capacitor_SMD:C_0603_1608Metric_Pad1.08x0.95mm_HandSolder","YAGEO","CC0603KRX7R7BB105"
"C56","1uF","Capacitor_SMD:C_0603_1608Metric_Pad1.08x0.95mm_HandSolder","YAGEO","CC0603KRX7R7BB105"
"C57","1uF","Capacitor_SMD:C_0603_1608Metric_Pad1.08x0.95mm_HandSolder","YAGEO","CC0603KRX7R7BB105"
"C58","1uF","Capacitor_SMD:C_0603_1608Metric_Pad1.08x0.95mm_HandSolder","YAGEO","CC0603KRX7R7BB105"
"C59","10nF","Capacitor_SMD:C_0603_1608Metric_Pad1.08x0.95mm_HandSolder","Murata Electronics","GCM188R71H103KA37J"
"C60","2.2nF","Capacitor_SMD:C_0603_1608Metric_Pad1.08x0.95mm_HandSolder","KEMET","C0603X222F4HACTU"
"C61","2.2nF","Capacitor_SMD:C_0603_1608Metric_Pad1.08x0.95mm_HandSolder","KEMET","C0603X222F4HACTU"
"C62","2.2nF","Capacitor_SMD:C_0603_1608Metric_Pad1.08x0.95mm_HandSolder","KEMET","C0603X222F4HACTU"
"C63","2.2nF","Capacitor_SMD:C_0603_1608Metric_Pad1.08x0.95mm_HandSolder","KEMET","C0603X222F4HACTU"
"C64","2.2nF","Capacitor_SMD:C_0603_1608Metric_Pad1.08x0.95mm_HandSolder","KEMET","C0603X222F4HACTU"
"C65","2.2nF","Capacitor_SMD:C_0603_1608Metric_Pad1.08x0.95mm_HandSolder","KEMET","C0603X222F4HACTU"
"C66","2.2nF","Capacitor_SMD:C_0603_1608Metric_Pad1.08x0.95mm_HandSolder","KEMET","C0603X222F4HACTU"
"C67","2.2nF","Capacitor_SMD:C_0603_1608Metric_Pad1.08x0.95mm_HandSolder","KEMET","C0603X222F4HACTU"
"C68","2.2nF","Capacitor_SMD:C_0603_1608Metric_Pad1.08x0.95mm_HandSolder","KEMET","C0603X222F4HACTU"
"C69","2.2nF","Capacitor_SMD:C_0603_1608Metric_Pad1.08x0.95mm_HandSolder","KEMET","C0603X222F4HACTU"
"C70","2.2nF","Capacitor_SMD:C_0603_1608Metric_Pad1.08x0.95mm_HandSolder","KEMET","C0603X222F4HACTU"
"C71","2.2nF","Capacitor_SMD:C_0603_1608Metric_Pad1.08x0.95mm_HandSolder","KEMET","C0603X222F4HACTU"
"C72","2.2nF","Capacitor_SMD:C_0603_1608Metric_Pad1.08x0.95mm_HandSolder","KEMET","C0603X222F4HACTU"
"C73","100nF","Capacitor_SMD:C_0603_1608Metric_Pad1.08x0.95mm_HandSolder","YAGEO","CC0603MRX7R9BB104"
"C74","100nF","Capacitor_SMD:C_0603_1608Metric_Pad1.08x0.95mm_HandSolder","YAGEO","CC0603MRX7R9BB104"
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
